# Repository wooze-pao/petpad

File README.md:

# The petpad

- petpad is a 12-key macropad with a rotary encoder, built around the Seeed XIAO RP2040 microcontroller. I will use it for daliy shortcut. like Copy etc.

## Renders 

- case

- pcb

---
## PCB Design
- Uses matrix scanning circuit with 12 1N4148 diodes to prevent ghosting key
---
## BOM
| **Component**          | **Qty** |
|------------------------|---------|
| **XIAO RP2040**        | 1       |
| **Rotary Encoder**     | 1       |
| **Cherry MX Switches** | 12      |
| **PCB**                | 1       |
| **Diodes (1N4148)**    | 12      |
| **M3x8 Bolt**          | 4       |

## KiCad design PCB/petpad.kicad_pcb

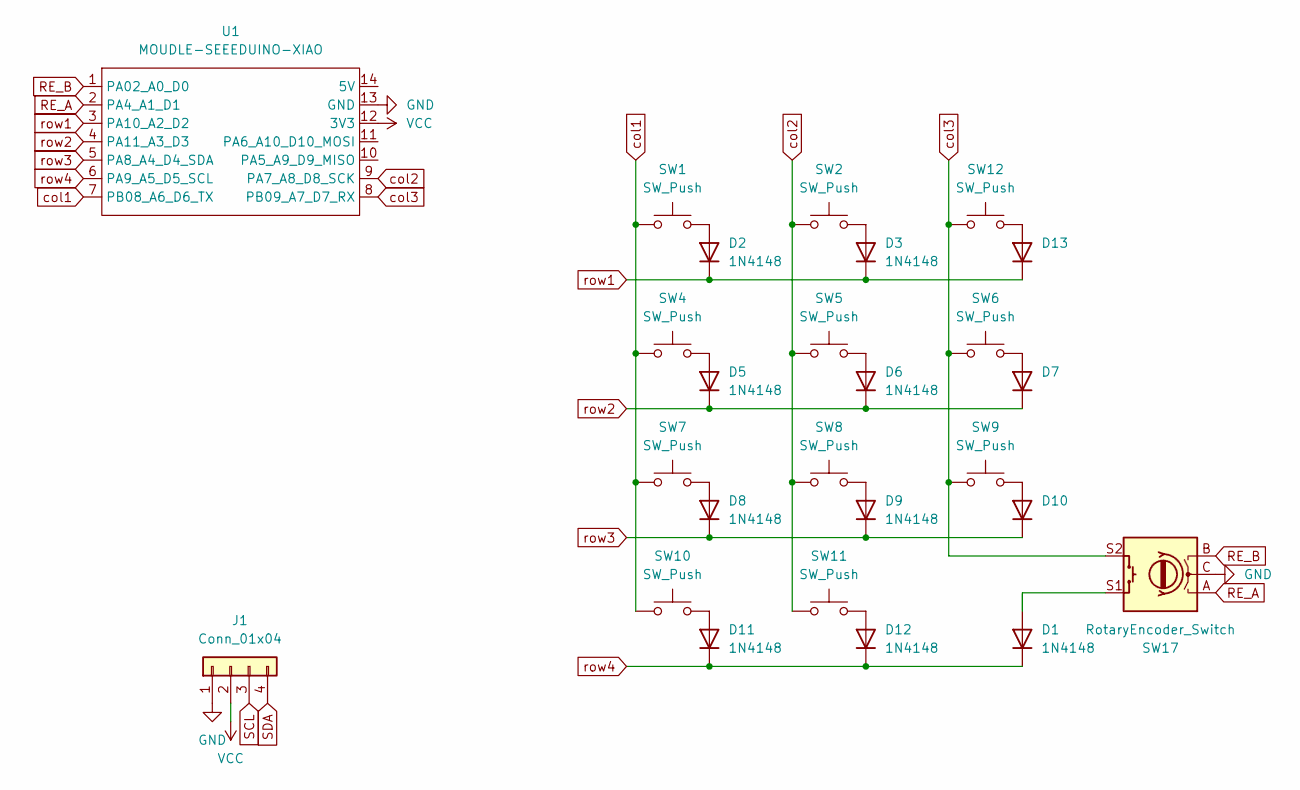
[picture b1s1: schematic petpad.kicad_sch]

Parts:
D1, D2, D3, D5, D6, D7, D8, D9, D10, D11, D12, D13: 1N4148; D_DO-35_SOD27_P7.62mm_Horizontal
J1: Conn_01x04; SSD1306-0.91-OLED-4pin-128x32
SW1, SW2, SW4, SW5, SW6, SW7, SW8, SW9, SW10, SW11, SW12: SW_Push; SW_Cherry_MX_1.00u_PCB
SW17: RotaryEncoder_Switch; RotaryEncoder_Alps_EC11E-Switch_Vertical_H20mm
U1: MOUDLE-SEEEDUINO-XIAO; XIAO-Generic-Hybrid-14P-2.54-21X17.8MM

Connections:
GND: J1.1, SW17.C, U1.13 (GND)
unnamed: D1.2 (A), SW17.S1
unnamed: D2.2 (A), SW1.2
unnamed: D3.2 (A), SW2.2
unnamed: D5.2 (A), SW4.2
unnamed: D6.2 (A), SW5.2
unnamed: D7.2 (A), SW6.2
unnamed: D8.2 (A), SW7.2
unnamed: D9.2 (A), SW8.2
unnamed: D10.2 (A), SW9.2
unnamed: D11.2 (A), SW10.2
unnamed: D12.2 (A), SW11.2
unnamed: D13.2 (A), SW12.2
RE_A: SW17.A, U1.2 (PA4_A1_D1)
RE_B: SW17.B, U1.1 (PA02_A0_D0)
SCL: J1.3, U1.11 (PA6_A10_D10_MOSI)
SDA: J1.4, U1.10 (PA5_A9_D9_MISO)
VCC: J1.2, U1.12 (3V3)
col1: SW1.1, SW4.1, SW7.1, SW10.1, U1.7 (PB08_A6_D6_TX)
col2: SW2.1, SW5.1, SW8.1, SW11.1, U1.9 (PA7_A8_D8_SCK)
col3: SW6.1, SW9.1, SW12.1, SW17.S2, U1.8 (PB09_A7_D7_RX)
row1: D2.1 (K), D3.1 (K), D13.1 (K), U1.3 (PA10_A2_D2)
row2: D5.1 (K), D6.1 (K), D7.1 (K), U1.4 (PA11_A3_D3)
row3: D8.1 (K), D9.1 (K), D10.1 (K), U1.5 (PA8_A4_D4_SDA)
row4: D1.1 (K), D11.1 (K), D12.1 (K), U1.6 (PA9_A5_D5_SCL)

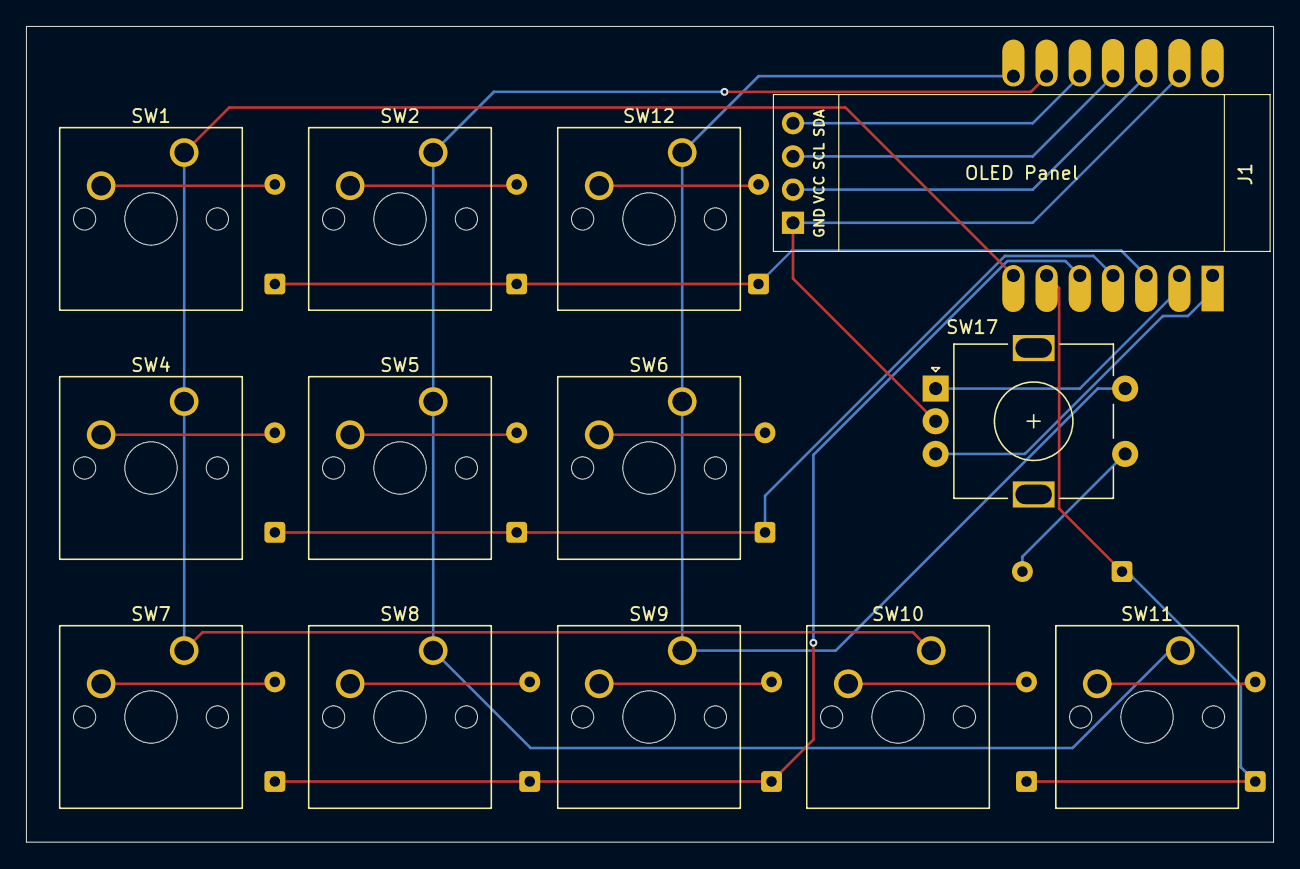
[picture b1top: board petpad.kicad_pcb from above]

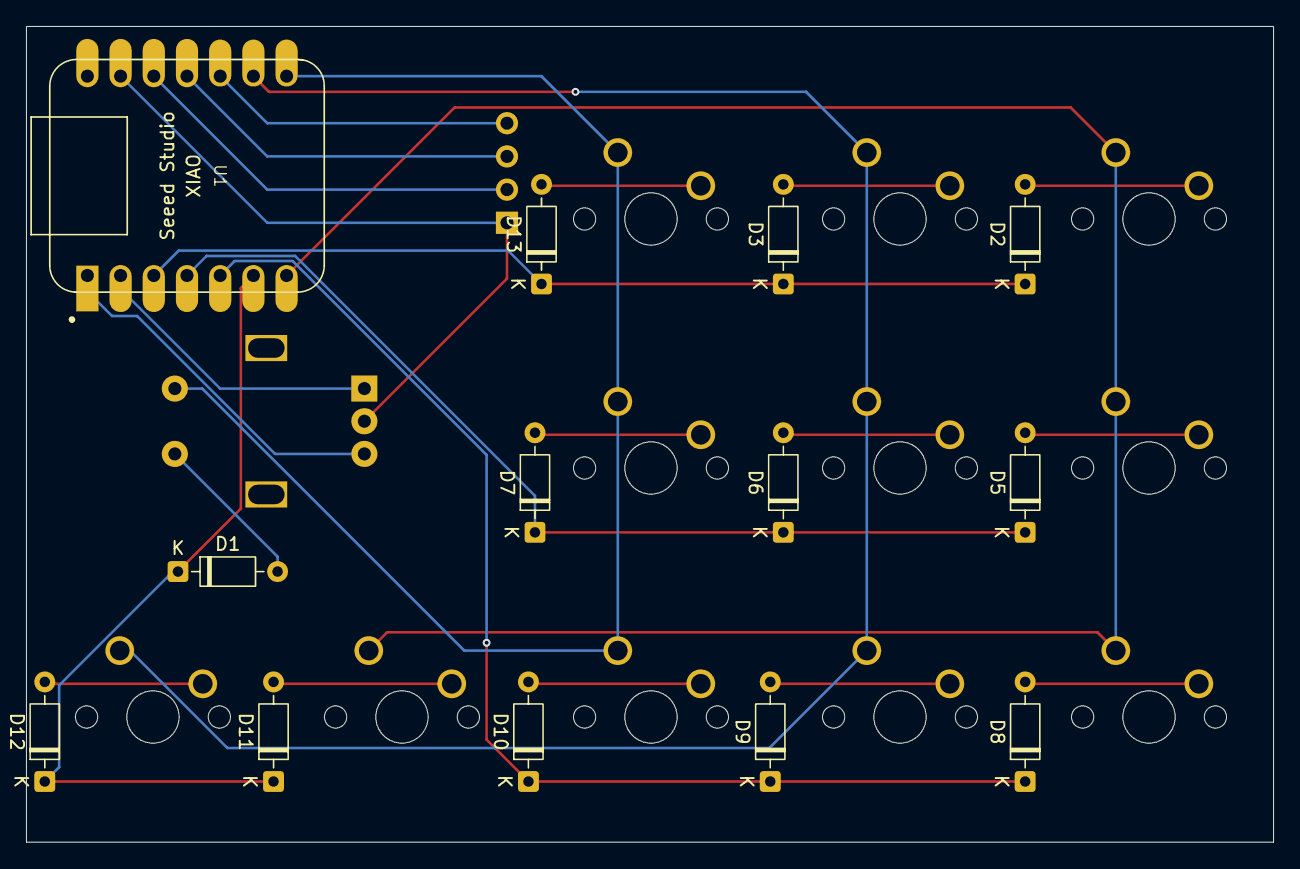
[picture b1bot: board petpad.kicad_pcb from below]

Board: 2 copper layers, 95.4 x 62.4 mm, 26 parts (13 on the bottom side), 25 nets.
